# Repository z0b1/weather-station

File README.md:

# weather-station
I'm presenting my project of a Field Weather Station containing anemometers and wind direction sensors, also ambient temp. and humidity sensors with a UHF transmitter in the field and an at home reciever(rtl-sdr). This also includes an RPi 4 (4GB RAM) that is recieving satellite images and displaying them in a mobile phone app.
# Why a weather station-Short Story
I live in the countryside and my family has large fruit plantations. By the microclimate of my area strong frosts in the spring time are common, that quite often hurts the fruits. We solve this issue by turning on our watering systems(the ground water keeps around 12 degrees Celsius at all times), but also by using air heaters to warm the area. So instead of waking up every 30 minutes to check the temps and having to go outside this idea was born. Main goal is that the weather station sends me phone notifications to a custom website/app. The weather station is located atleast 500m away from the house so the trick was getting reliable power, which I solved using a solar panel and a Lead Acid battery.
# How it functions 
Using an Arduino Nano I read the data from the sensors and send it with my UHF transmitter using ASK modulation(to be changed to FSK if too much interferences). At home using a reciever and an RPi 4 Model B (4GB), RTL SDR V4 and a homemade quadrifillar helix antenna to recieve satellite images and a Nagoya antenna for the UHF signals. Compare it and display on the website/app using the RPi.
# What might be added 
Using local LLM's to recognize cloud and other patterns to predict weather more accurately.

# Pictures

# NAPRED ZVEZDO

# The BOM

| Reference | Qty | Value | Price | Link | Info | Datasheet |
|---|---|---|---|---|---|---|
| A1 | 1 | Arduino Nano | € 5.16 | [Link](https://www.aliexpress.com/item/1005009848194286.html) | | [Link](https://content.arduino.cc/assets/NANOEveryV3.0_sch.pdf) |
| AE1 | 1 | Antenna Shielded SMA | € 0.00 | [Link](https://www.aliexpress.com/item/1005008813991595.html) | I already have | ~ |
| AE2 | 2 | Nagoya NA-771 | € 7.47 | [Link](https://www.aliexpress.com/item/1005008660133810.html?spm=a2g0o.productlist.main.1.54332Rrn2RrnbS&algo_pvid=6b1cd6b7-e759-4554-baba-a451a18d1cca&algo_exp_id=6b1cd6b7-e759-4554-baba-a451a18d1cca-0&pdp_ext_f=%7B%22order%22%3A%22663%22%2C%22spu_best_type%22%3A%22order%22%2C%22eval%22%3A%221%22%2C%22orig_sl_item_id%22%3A%221005008660133810%22%2C%22orig_item_id%22%3A%221005005862057777%22%2C%22fromPage%22%3A%22search%22%7D&pdp_npi=6%40dis%21EUR%219.50%214.75%21%21%2175.96%2137.98%21%4021BVTrB47erypG3tevi1U9Fv6BbNUBEiuiX%2112000046135982236%21sea%21SRB%210%21ABX%211%210%21n_tag%3A-29910%3Bd%3A3d40ec8a%3Bm03_new_user%3A-29895&curPageLogUid=peroKELiN18w&utparam-url=scene%3Asearch%7Cquery_from%3A%7Cx_object_id%3A1005008660133810%7C_p_origin_prod%3A1005005862057777) | High Gain Handheld Antenna | ~ |
| BT1 | 1 | 12V 5Ah Lead Acid | € 11.84 | [Link](https://borikplus.rs/proizvodi/olovne-baterije/ritar-rt1250-olovna-vrla-baterija-12v-5ah/) | Alternative capacity | ~ |
| C1 | 1 | 470uF | € 0.00 | [Link](https://www.aliexpress.com/item/1005008244407175.html) | I already have | ~ |
| C2 | 1 | 100uF | € 0.00 | [Link](https://www.aliexpress.com/item/1005005661484224.html) | I already have | ~ |
| C3 | 1 | 2pF | - | | | ~ |
| C4 | 1 | 2.2pF | - | | | ~ |
| C5 | 1 | 10pF | - | | | ~ |
| C6 | 1 | 470pF | - | | | ~ |
| D1 | 1 | LED_R | € 0.00 | [Link](https://www.aliexpress.com/item/1005010315277808.html) | I already have | ~ |
| J1, J2 | 1 | RS485 ANEMOMETER | € 26.53 | [Link](https://www.aliexpress.com/item/1005007059408469.html?spm=a2g0o.productlist.main.2.4a033928CMF5XY&algo_pvid=716ca457-5aab-4316-b2cb-04b983bb9b31&algo_exp_id=716ca457-5aab-4316-b2cb-04b983bb9b31-1&pdp_ext_f=%7B%22order%22%3A%2222%22%2C%22eval%22%3A%221%22%25) | RS485 type | ~ |
| J4 | 1 | RS485 WIND DIRECTION | € 23.82 | [Link](https://www.aliexpress.com/item/1005007059408469.html?spm=a2g0o.productlist.main.2.4a033928CMF5XY&algo_pvid=716ca457-5aab-4316-b2cb-04b983bb9b31&algo_exp_id=716ca457-5aab-4316-b2cb-04b983bb9b31-1&pdp_ext_f=%7B%22order%22%3A%2222%22%2C%22eval%22%3A%221%22%25) | RS485 type | ~ |
| U4 | 1 | SDLA12TA | € 6.86 | [Link](https://www.aliexpress.com/item/1005006641063540.html?spm=a2g0o.productlist.main.2.27095885CkBPLU&algo_pvid=e4be5066-8354-41d3-922b-3ee448c878b3&algo_exp_id=e4be5066-8354-41d3-922b-3ee448c878b3-1&pdp_ext_f=%7B%22order%22%3A%2225%22%2C%22eval%22%3A%221%22%25) | | [Link](https://easyeda.com/component/451d05428ff8431fb9c594829dfd0fbf) |
| R1 | 1 | 2k1 | € 0.00 | [Link](https://www.aliexpress.com/item/1005010688244614.html?spm=a2g0o.productlist.main.2.7d8fG8tEG8tEk2&algo_pvid=e197ad8d-f3f6-47ee-a63e-3a9a69ddded3&algo_exp_id=e197ad8d-f3f6-47ee-a63e-3a9a69ddded3-1&pdp_ext_f=%7B%22order%22%3A%225%22%2C%22eval%22%3A%221%22%252) | I already have | ~ |
| R2 | 1 | 220| - | | | ~ |
| R3, R6 | 2 | 10K | - | | | ~ |
| R5 | 1 | 47K | - | | | ~ |
| R7 | 1 | 120 | - | | | ~ |
| SC1 | 1 | Solar cell | € 23.00 | [Link]([(https://www.aliexpress.com/item/1005009242077484.html?spm=a2g0o.productlist.main.3.71ca1ebc8ezGr6&algo_pvid=63f95f2c-0c5b-44aa-aa5d-ec7286dc5a43&algo_exp_id=63f95f2c-0c5b-44aa-aa5d-ec7286dc5a43-2&pdp_ext_f=%7B%22order%22%3A%2219%22%2C%22eval%22%3A%221%22%2C%22fromPage%22%3A%22search%22%7D&pdp_npi=6%40dis%21RSD%214034.96%212663.12%21%21%21249.92%21164.95%21%40211b618e17728801284725500e8514%2112000048444689432%21sea%21SRB%212579406706%21ABX%211%210%21n_tag%3A-29910%3Bd%3Aaa499002%3Bm03_new_user%3A-29895&curPageLogUid=gPeGyl2tXnC8&utparam-url=scene%3Asearch%7Cquery_from%3A%7Cx_object_id%3A1005009242077484%7C_p_origin_prod%3A)]) | 15W 12V | ~ |
| U1 | 1 | DC-DC Buck Converter PTN78000HAZ | € 3.02 | [Link](https://www.aliexpress.com/item/1005008535110639.html?spm=a2g0o.productlist.main.1.ae99324aHG01bo&algo_pvid=98ef4908-7110-49f7-bd78-fd48493daabe&algo_exp_id=98ef4908-7110-49f7-bd78-fd48493daabe-0&pdp_ext_f=%7B%22order%22%3A%22753%22%2C%22eval%22%3A%221%22%2C%22fromPage%22%3A%22search%22%7D&pdp_npi=6%40dis%21EUR%2118.87%213.02%21%21%21150.83%2124.12%21%40211b617b17712049515593924e2a90%2112000045604067614%21sea%21SRB%210%21ABX%211%210%21n_tag%3A-29910%3Bd%3A3d40ec8a%3Bm03_new_user%3A-29895%3BpisId%3A5000000198944678&curPageLogUid=FJqewnV1My1f&utparam-url=scene%3Asearch%7Cquery_from%3A%7Cx_object_id%3A1005008535110639%7C_p_origin_prod%3A#nav-specification) | Voltage Regulator | ~ |
| U2 | 1 | MAX485E | € 4.39 | [Link](https://www.aliexpress.com/item/1005008248138246.html?spm=a2g0o.productlist.main.3.50414ee34ANwSC&algo_pvid=91f3ea3b-89b0-416b-b821-3a5b0b836404&algo_exp_id=91f3ea3b-89b0-416b-b821-3a5b0b836404-2&pdp_ext_f=%7B%22order%22%3A%224614%22%2C%22spu_best_type%22%3A%22order%22%2C%22eval%22%3A%221%22%2C%22orig_sl_item_id%22%3A%221005008248138246%22%2C%22orig_item_id%22%3A%221005008332469260%22%2C%22fromPage%22%3A%22search%22%7D&pdp_npi=6%40dis%21EUR%218.78%214.39%21%21%2170.18%2135.09%21%40211b615317711213649861629e601f%2112000044371383487%21sea%21SRB%210%21ABX%211%210%21n_tag%3A-29910%3Bd%3A3d40ec8a%3Bm03_new_user%3A-29895&curPageLogUid=iT1tcIOUDtud&utparam-url=scene%3Asearch%7Cquery_from%3A%7Cx_object_id%3A1005008248138246%7C_p_origin_prod%3A1005008332469260) | RS485 Translate | [Link](https://datasheets.maximintegrated.com/en/ds/MAX1487E-MAX491E.pdf) |
| U3 | 1 | DHT22 | € 3.01 | [Link](https://www.aliexpress.com/item/1005012000000000.html) | Temp & Humidity sensor | [Link](http://akizukidenshi.com/download/ds/aosong/AM2302.pdf) |
| RF1 | 1 | 433MHz RF Kit | € 0.00 | [Link](https://www.aliexpress.com/item/1005005853468512.html) | Transmitter + Receiver(i already have) | |
| U5 | 2 | DS18B20 | € 5.59 | [Link](https://www.aliexpress.com/item/1005010363252763.html?spm=a2g0o.productlist.main.3.29524241FUBE8k&algo_pvid=3deaecd0-814a-478f-b2ff-2f3b8ef2c44d&algo_exp_id=3deaecd0-814a-478f-b2ff-2f3b8ef2c44d-2&pdp_ext_f=%7B%22order%22%3A%2274%22%2C%22eval%22%3A%221%22%2C%22fromPage%22%3A%22search%22%7D&pdp_npi=6%40dis%21EUR%219.80%210.85%21%21%2178.32%216.80%21%40211b61a417711198131738996e5d08%2112000052189971493%21sea%21SRB%210%21ABX%211%210%21n_tag%3A-29910%3Bd%3A3d40ec8a%3Bm03_new_user%3A-29895%3BpisId%3A5000000198944678&curPageLogUid=zeX5XbhmfOld&utparam-url=scene%3Asearch%7Cquery_from%3A%7Cx_object_id%3A1005010363252763%7C_p_origin_prod%3A) | Waterproof Temp Sensor | [Link](https://datasheets.maximintegrated.com/en/ds/DS18B20.pdf) |
| U6 | 1 | Raspberry Pi 4 Model B (4GB) | € 82.56 | [Link](https://www.aliexpress.com/item/1005012300000000.html) | Receiver Host | ~ |
| U7 | 1 | RTL-SDR V4 | € 35.39 | [Link](https://www.aliexpress.com/item/1005005952682051.html?spm=a2g0o.productlist.main.1.48a66fc2gUYayG&algo_pvid=6d388bf8-3a0e-4b6f-b9bc-0c79559edaf9&algo_exp_id=6d388bf8-3a0e-4b6f-b9bc-0c79559edaf9-0&pdp_ext_f=%7B%22order%22%3A%224343%22%2C%22spu_best_type%22%3A%22price%22%2C%22eval%22%3A%221%22%2C%22fromPage%22%3A%22search%22%7D&pdp_npi=6%40dis%21EUR%2135.39%2129.35%21%21%2140.99%2133.99%21%40211b629217712043605765600e6638%2112000035000774710%21sea%21SRB%210%21ABX%211%210%21n_tag%3A-29910%3Bd%3A3d40ec8a%3Bm03_new_user%3A-29895%3BpisId%3A5000000198944678&curPageLogUid=9zutLPD0Zz1y&utparam-url=scene%3Asearch%7Cquery_from%3A%7Cx_object_id%3A1005005952682051%7C_p_origin_prod%3A) | Official Receiver | ~ |
| AC1 | 1 | Micro-Type Diplexer Duplex Filter | € 11.09 | [Link](https://www.aliexpress.com/item/1005005862057777.html?spm=a2g0o.productlist.main.4.54332Rrn2RrnbS&algo_pvid=6b1cd6b7-e759-4554-baba-a451a18d1cca&algo_exp_id=6b1cd6b7-e759-4554-baba-a451a18d1cca-4&pdp_ext_f=%7B%22order%22%3A%2272%22%2C%22eval%22%3A%221%22%25) | 10W V/U 2m 70cm | ~ |
| PCB | 1 | JLCPCB PCB Manufacturing | € 19.61 | [Link]| $20.75 | ~ |

**Grand Total**: € 269.34 ($ 285.50)  
**Grand Total (Including shipping/VAT)**: € 274.87 ($ 291.36)

**NOTE: IN THE GRAND TOTAL IS INCLUDED THE PRICE OF JLCPCB PCB MANUFACTURING**

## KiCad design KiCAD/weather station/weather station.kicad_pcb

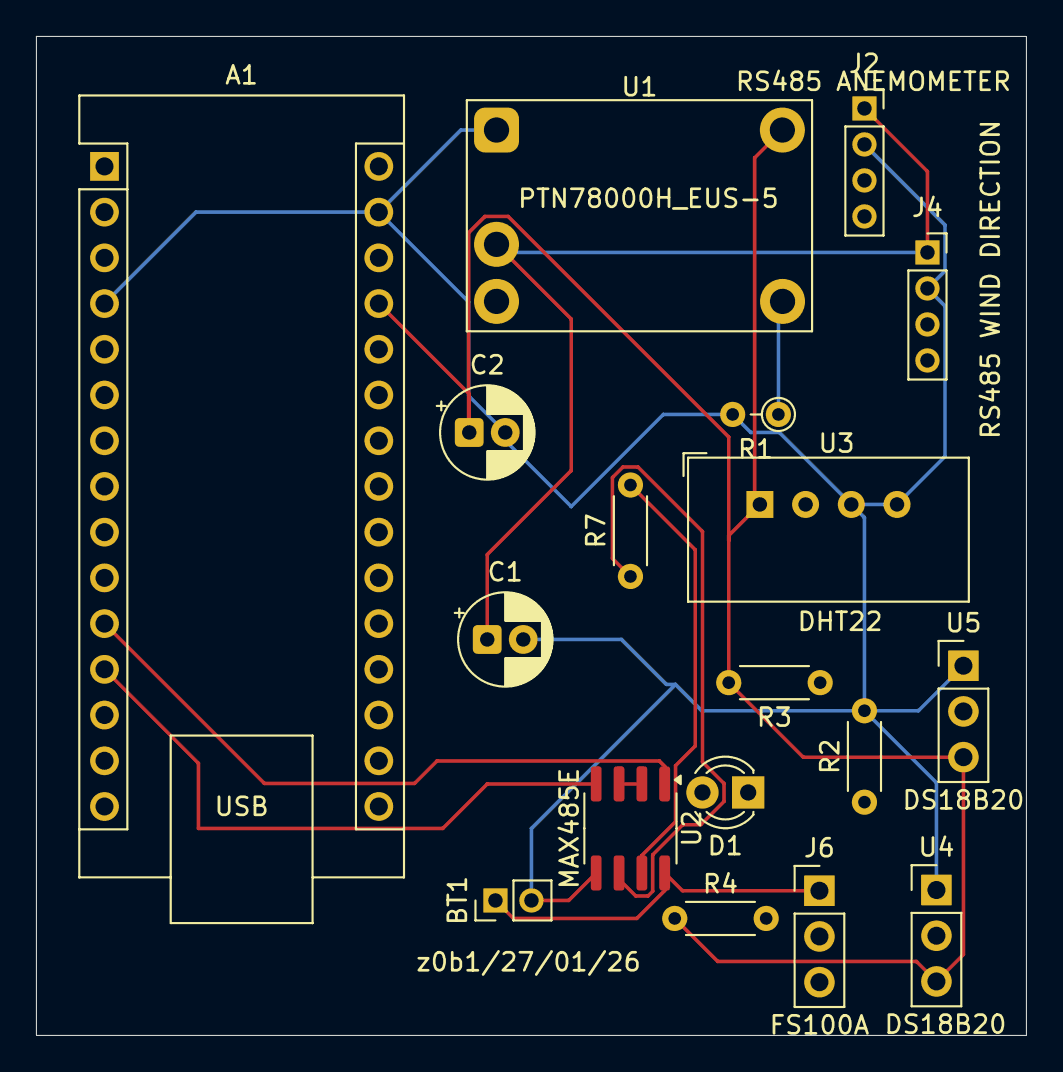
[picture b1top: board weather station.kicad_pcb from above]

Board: 4 copper layers, 55.0 x 55.5 mm, 18 parts (0 on the bottom side), 14 nets.

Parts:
A1: Arduino_Nano_Every; Arduino_Nano
BT1: 12V; PinHeader_1x02_P2.00mm_Vertical
C1: 470u; CP_Radial_D5.0mm_P2.00mm
C2: 100u; CP_Radial_D5.0mm_P2.00mm
D1: LED_R; LED_D3.0mm
J2: RS485 ANEMOMETER; PinSocket_1x04_P2.00mm_Vertical
J4: RS485 WIND DIRECTION; PinSocket_1x04_P2.00mm_Vertical
J6: FS100A; PinHeader_1x03_P2.54mm_Vertical
R1: 2k1; R_Axial_DIN0204_L3.6mm_D1.6mm_P2.54mm_Vertical
R2: 220; R_Axial_DIN0204_L3.6mm_D1.6mm_P5.08mm_Horizontal
R3: 10K; R_Axial_DIN0204_L3.6mm_D1.6mm_P5.08mm_Horizontal
R4: 2K2; R_Axial_DIN0204_L3.6mm_D1.6mm_P5.08mm_Horizontal
R7: 120; R_Axial_DIN0204_L3.6mm_D1.6mm_P5.08mm_Horizontal
U1: PTN78000H_EUS-5; Texas_EUS_R-PDSS-T5_THT
U2: MAX485E; SOIC-8_3.9x4.9mm_P1.27mm
U3: DHT22; ASAIR_AM2302_P2.54mm_Vertical
U4, U5: DS18B20; PinHeader_1x03_P2.54mm_Vertical

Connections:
+12V: BT1.1 (+), C1.1, J2.1, J4.1, J6.1, U1.2 (VI), U2.8 (VCC)
A+: J2.3, J4.3, R7.1, U2.6 (A)
B-: J2.4, J4.4, R7.2, U2.7 (B)
D8: A1.11 (D8), U2.1 (RO)
D9: A1.12 (D9), U2.4 (DI)
GND: A1.4 (GND), A1.29 (GND), BT1.2 (-), C1.2, C2.2, J2.2, J4.2, R1.2, R2.2, U1.1 (GND), U2.5 (GND), U3.3 (GND), U3.4 (GND), U4.1 (GND), U5.1 (GND)
unnamed: A1.27 (+5V), C2.1, R3.2, R4.1, U1.5 (VO), U3.1 (VDD), U4.3 (V_{DD}), U5.3 (V_{DD})
unnamed: A1.5 (D2), R4.2, U4.2 (DQ), U5.2 (DQ)
unnamed: A1.6 (D3), J6.2
unnamed: A1.7 (D4), R3.1, U3.2 (SDA)
unnamed: A1.13 (D10), D1.2 (A)
unnamed: D1.1 (K), R2.1
unnamed: R1.1, U1.4 (Vo_Adj)
unnamed: U2.2 (~RE), U2.3 (DE)

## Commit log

2026-01-27 Enhance README with project details and future plans
    Expanded the README with a short story about the weather station's purpose, its functionality, and potential future improvements.
2026-01-27 Add BOM section to README
    Added a section for the Bill of Materials (BOM) in the README.
2026-02-09 Fixing the readme
2026-02-13 Code for the RPi
2026-02-13 Changing the readme
2026-02-13 making the code prettier
2026-02-15 PCB update and firmware update
2026-02-15 PCB PNG
2026-02-15 refining the code and changing from OOK to ASK
2026-02-15 adding some images
2026-02-15 made the BOM table in the readme
2026-02-15 Updating BOM
2026-02-15 Optimized the BOM and the tracking code, should work with ntfy.sh
2026-02-15 Android app developing and a tutorial for when i connect the rpi to the app
2026-02-15 Giant changes to the app UI
2026-02-15 Added a 10cm below and above temp sensors(standard for agricultural meteorology)
2026-02-15 removed duck.sh as i will be using zrok.io
2026-02-15 Edited the tutorial
2026-02-16 JLCPCB sc
2026-02-16 BOM change
2026-02-16 Finalized the BOM
2026-02-16 A frost alert addition to my android app
2026-02-16 added the apk
2026-02-16 New features in the app.
2026-02-16 Some small app tweakings
2026-02-16 some cool readme additions
2026-02-20 just changed something in the reciever because of SatDump compatibility and cloned the rep to linux
2026-02-20 added some features and fixed indent issues
2026-02-20 debugging pythone code
2026-02-20 testing sum features
2026-02-20 test again
2026-03-06 fixed the missing images
2026-03-06 Just changed pictures to Pictures in the Readme
2026-03-07 Moved the BOM to the bottom of the readme
2026-03-07 Fix solar cell link in README.md
    Updated the link for the solar cell in the README.
